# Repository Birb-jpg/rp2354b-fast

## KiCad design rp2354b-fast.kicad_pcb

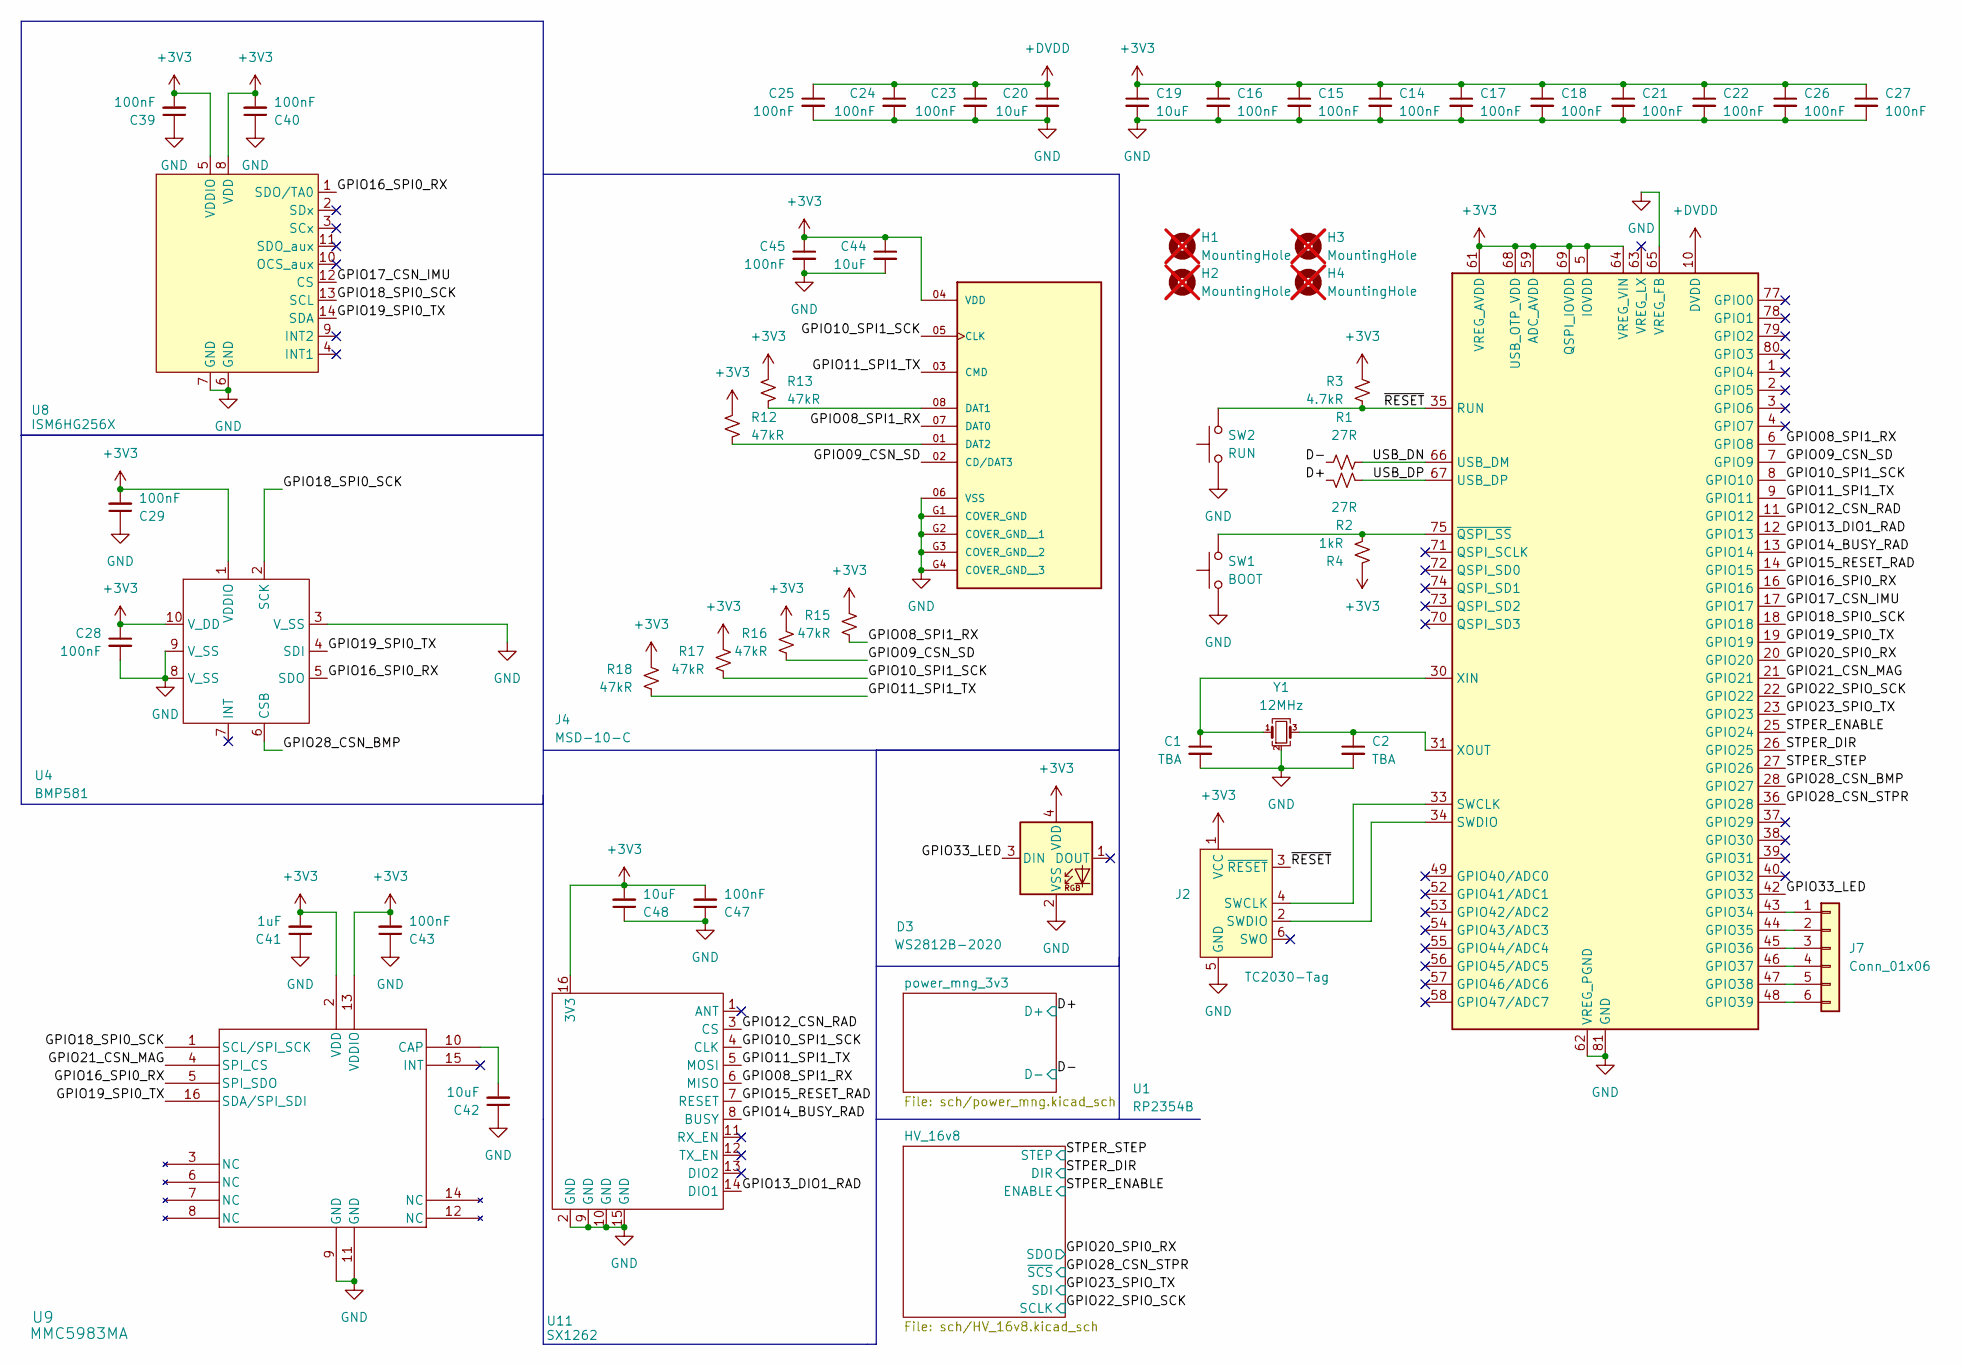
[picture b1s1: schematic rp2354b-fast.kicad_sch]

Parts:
C1, C2: TBA; C_0402_1005Metric
C14, C15, C16, C17, C18, C21, C22, C23, C24, C25, C26, C27, C28, C29, C39, C40, C43, C45, C47: 100nF; C_0402_1005Metric
C19, C20, C42, C44, C48: 10uF; C_0402_1005Metric
C41: 1uF; C_0402_1005Metric
D3: WS2812B-2020; LED_WS2812B-2020_PLCC4_2.0x2.0mm
H1, H2, H3, H4: MountingHole; MountingHole_4.3mm_M4; not fitted
J2: TC2030-Tag; Tag-Connect_TC2030-IDC-NL_2x03_P1.27mm_Vertical
J4: MSD-10-C; PARTREV 1.0
J7: Conn_01x06; PinHeader_1x06_P2.54mm_Vertical
R1, R2: 27R; R_0402_1005Metric
R3: 4.7kR; R_0402_1005Metric
R4: 1kR; R_0402_1005Metric
R12, R13, R15, R16, R17, R18: 47kR; R_0402_1005Metric
SW1: BOOT; SW_Push_1P1T_NO_Vertical_Wuerth_434133025816
SW2: RUN; SW_Push_1P1T_NO_Vertical_Wuerth_434133025816
U1: RP2354B; QFN-80-1EP_10x10mm_P0.4mm_EP3.4x3.4mm
U4: BMP581; QFN10_BMP581_BOS
U8: ISM6HG256X; LGA-14_3x2.5mm_P0.5mm_LayoutBorder3x4y
U9: MMC5983MA; LGA-16_3x3mm_P0.5mm
U11: SX1262; CORE-1262
Y1: 12MHz; Crystal_SMD_SeikoEpson_TSX3225-4Pin_3.2x2.5mm

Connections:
+3V3: C14.1, C15.1, C16.1, C17.1, C18.1, C19.1, C21.1, C22.1, C26.1, C27.1, C28.1, C29.2, C39.2, C40.2, C41.2, C43.2, C44.1, C45.1, C47.2, C48.2, D3.4 (VDD), J2.1 (VCC), J4.04 (VDD), R3.1, R4.1, R12.1, R13.1, R15.1, R16.1, R17.1, R18.1, U1.5 (IOVDD), U1.15 (IOVDD), U1.24 (IOVDD), U1.29 (IOVDD), U1.41 (IOVDD), U1.50 (IOVDD), U1.59 (ADC_AVDD), U1.60 (IOVDD), U1.61 (VREG_AVDD), U1.64 (VREG_VIN), U1.68 (USB_OTP_VDD), U1.69 (QSPI_IOVDD), U1.76 (IOVDD), U4.1 (VDDIO), U4.10 (V_DD), U8.5 (VDDIO), U8.8 (VDD), U9.2 (VDD), U9.13 (VDDIO), U11.16 (3V3); also elsewhere on the board
+DVDD: C20.1, C23.1, C24.1, C25.1, U1.10 (DVDD), U1.32 (DVDD), U1.51 (DVDD); also elsewhere on the board
/D+: R2.2; also elsewhere on the board
/D-: R1.2; also elsewhere on the board
/GPIO08_SPI1_RX: J4.07 (DAT0), R15.2, U1.6 (GPIO8), U11.6 (MISO)
/GPIO09_CSN_SD: J4.02 (CD/DAT3), R16.2, U1.7 (GPIO9)
/GPIO10_SPI1_SCK: J4.05 (CLK), R17.2, U1.8 (GPIO10), U11.4 (CLK)
/GPIO11_SPI1_TX: J4.03 (CMD), R18.2, U1.9 (GPIO11), U11.5 (MOSI)
/GPIO12_CSN_RAD: U1.11 (GPIO12), U11.3 (CS)
/GPIO13_DIO1_RAD: U1.12 (GPIO13), U11.14 (DIO1)
/GPIO14_BUSY_RAD: U1.13 (GPIO14), U11.8 (BUSY)
/GPIO15_RESET_RAD: U1.14 (GPIO15), U11.7 (RESET)
/GPIO16_SPI0_RX: U1.16 (GPIO16), U4.5 (SDO), U8.1 (SDO/TA0), U9.5 (SPI_SDO)
/GPIO17_CSN_IMU: U1.17 (GPIO17), U8.12 (CS)
/GPIO18_SPI0_SCK: U1.18 (GPIO18), U4.2 (SCK), U8.13 (SCL), U9.1 (SCL/SPI_SCK)
/GPIO19_SPI0_TX: U1.19 (GPIO19), U4.4 (SDI), U8.14 (SDA), U9.16 (SDA/SPI_SDI)
/GPIO20_SPI0_RX: U1.20 (GPIO20); also elsewhere on the board
/GPIO21_CSN_MAG: U1.21 (GPIO21), U9.4 (SPI_CS)
/GPIO22_SPIO_SCK: U1.22 (GPIO22); also elsewhere on the board
/GPIO23_SPIO_TX: U1.23 (GPIO23); also elsewhere on the board
/GPIO28_CSN_BMP: U1.28 (GPIO27), U4.6 (CSB)
/GPIO28_CSN_STPR: U1.36 (GPIO28); also elsewhere on the board
/GPIO33_LED: D3.3 (DIN), U1.42 (GPIO33)
/STPER_DIR: U1.26 (GPIO25); also elsewhere on the board
/STPER_ENABLE: U1.25 (GPIO24); also elsewhere on the board
/STPER_STEP: U1.27 (GPIO26); also elsewhere on the board
/USB_DN: R1.1, U1.66 (USB_DM)
/USB_DP: R2.1, U1.67 (USB_DP)
/~RESET: J2.3 (~RESET), R3.2, SW2.2, U1.35 (RUN)
GND: C1.2, C2.2, C14.2, C15.2, C16.2, C17.2, C18.2, C19.2, C20.2, C21.2, C22.2, C23.2, C24.2, C25.2, C26.2, C27.2, C28.2, C29.1, C39.1, C40.1, C41.1, C42.1, C43.1, C44.2, C45.2, C47.1, C48.1, D3.2 (VSS), J2.5 (GND), J4.06 (VSS), J4.G1 (COVER_GND), J4.G2 (COVER_GND__1), J4.G3 (COVER_GND__2), J4.G4 (COVER_GND__3), SW1.1, SW2.1, U1.62 (VREG_PGND), U1.65 (VREG_FB), U1.81 (GND), U4.3 (V_SS), U4.8 (V_SS), U4.9 (V_SS), U8.6 (GND), U8.7 (GND), U9.9 (GND), U9.11 (GND), U11.2 (GND), U11.9 (GND), U11.10 (GND), U11.15 (GND), Y1.2 (G), Y1.4 (G); also elsewhere on the board
unnamed: J2.4 (SWCLK), U1.33 (SWCLK)
unnamed: J2.2 (SWDIO), U1.34 (SWDIO)
unnamed: J4.08 (DAT1), R13.2
unnamed: J4.01 (DAT2), R12.2
unnamed: J7.1, U1.43 (GPIO34)
unnamed: J7.2, U1.44 (GPIO35)
unnamed: J7.3, U1.45 (GPIO36)
unnamed: J7.4, U1.46 (GPIO37)
unnamed: J7.5, U1.47 (GPIO38)
unnamed: J7.6, U1.48 (GPIO39)
unnamed: C1.1, U1.30 (XIN), Y1.1
unnamed: C2.1, U1.31 (XOUT), Y1.3
unnamed: R4.2, SW1.2, U1.75 (~QSPI_SS)
unnamed: C42.2, U9.10 (CAP)

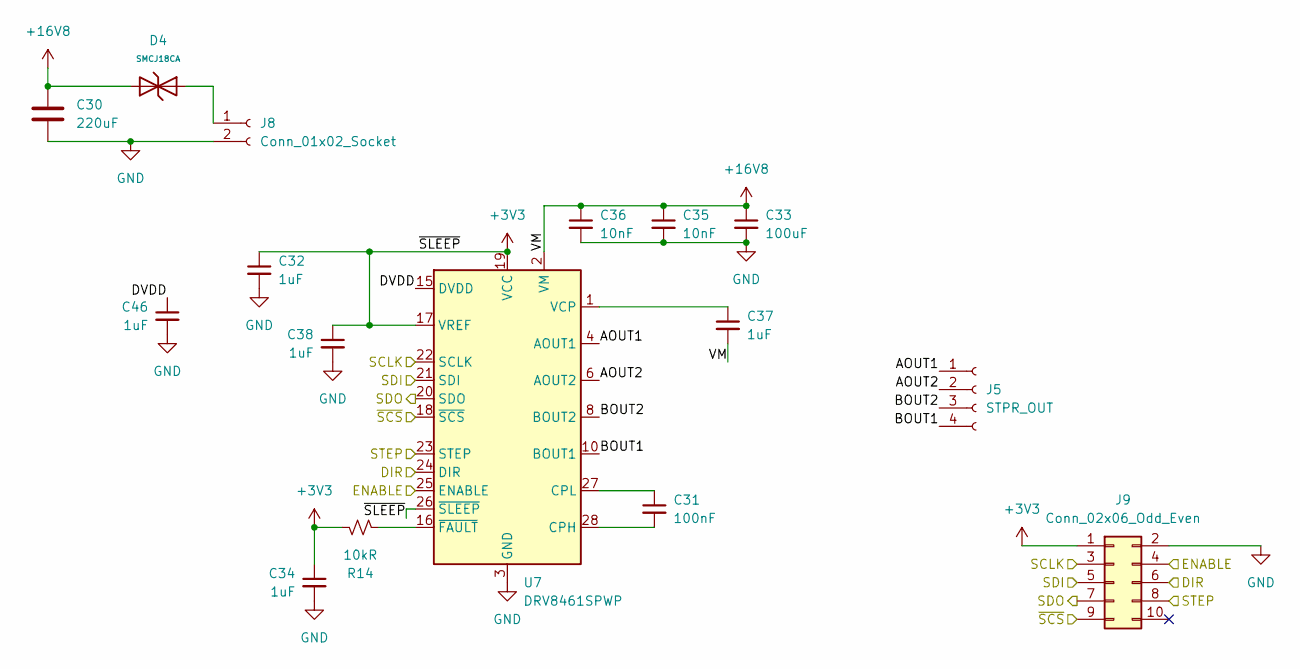
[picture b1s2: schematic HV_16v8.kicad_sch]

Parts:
C30: 220uF; CP_Radial_D8.0mm_P3.50mm
C31: 100nF; C_0402_1005Metric
C32, C34, C38, C46: 1uF; C_0402_1005Metric
C33: 100uF; C_1206_3216Metric
C35, C36: 10nF; C_1206_3216Metric
C37: 1uF; C_1206_3216Metric
D4: SMCJ18CA; D_SMC; Breakdown Voltage 22.1V; Part SMCJ18CA; LCSC C41411753
J5: STPR_OUT; JST_XA_B04B-XASK-1_1x04_P2.50mm_Vertical
J8: Conn_01x02_Socket; AMASS_XT30PW-M_1x02_P2.50mm_Horizontal
J9: Conn_02x06_Odd_Even; PinHeader_2x05_P2.54mm_Vertical
R14: 10kR; R_0402_1005Metric
U7: DRV8461SPWP; HTSSOP-28-1EP_4.4x9.7mm_P0.65mm_EP2.85x5.4mm_ThermalVias

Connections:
+3V3: C32.1, C34.1, C38.1, J9.1, R14.1, U7.17 (VREF), U7.19 (VCC), U7.26 (~SLEEP); also elsewhere on the board
+16V8: C30.1, C33.1, C35.1, C36.1, C37.2, D4.2, U7.2 (VM), U7.13 (VM)
/GPIO20_SPI0_RX: J9.7, U7.20 (SDO); also elsewhere on the board
/GPIO22_SPIO_SCK: J9.3, U7.22 (SCLK); also elsewhere on the board
/GPIO23_SPIO_TX: J9.5, U7.21 (SDI); also elsewhere on the board
/GPIO28_CSN_STPR: J9.9, U7.18 (~SCS); also elsewhere on the board
/HV_16v8/AOUT1: J5.1, U7.4 (AOUT1), U7.5 (AOUT1)
/HV_16v8/AOUT2: J5.2, U7.6 (AOUT2), U7.7 (AOUT2)
/HV_16v8/BOUT1: J5.4, U7.10 (BOUT1), U7.11 (BOUT1)
/HV_16v8/BOUT2: J5.3, U7.8 (BOUT2), U7.9 (BOUT2)
/HV_16v8/DVDD: C46.1, U7.15 (DVDD)
/STPER_DIR: J9.6, U7.24 (DIR); also elsewhere on the board
/STPER_ENABLE: J9.4, U7.25 (ENABLE); also elsewhere on the board
/STPER_STEP: J9.8, U7.23 (STEP); also elsewhere on the board
GND: C30.2, C32.2, C33.2, C34.2, C35.2, C36.2, C38.2, C46.2, J8.2, J9.2, U7.3 (GND), U7.12 (GND), U7.14 (GND), U7.29 (GND); also elsewhere on the board
unnamed: D4.1, J8.1
unnamed: C31.2, U7.28 (CPH)
unnamed: C31.1, U7.27 (CPL)
unnamed: C37.1, U7.1 (VCP)
unnamed: R14.2, U7.16 (~FAULT)

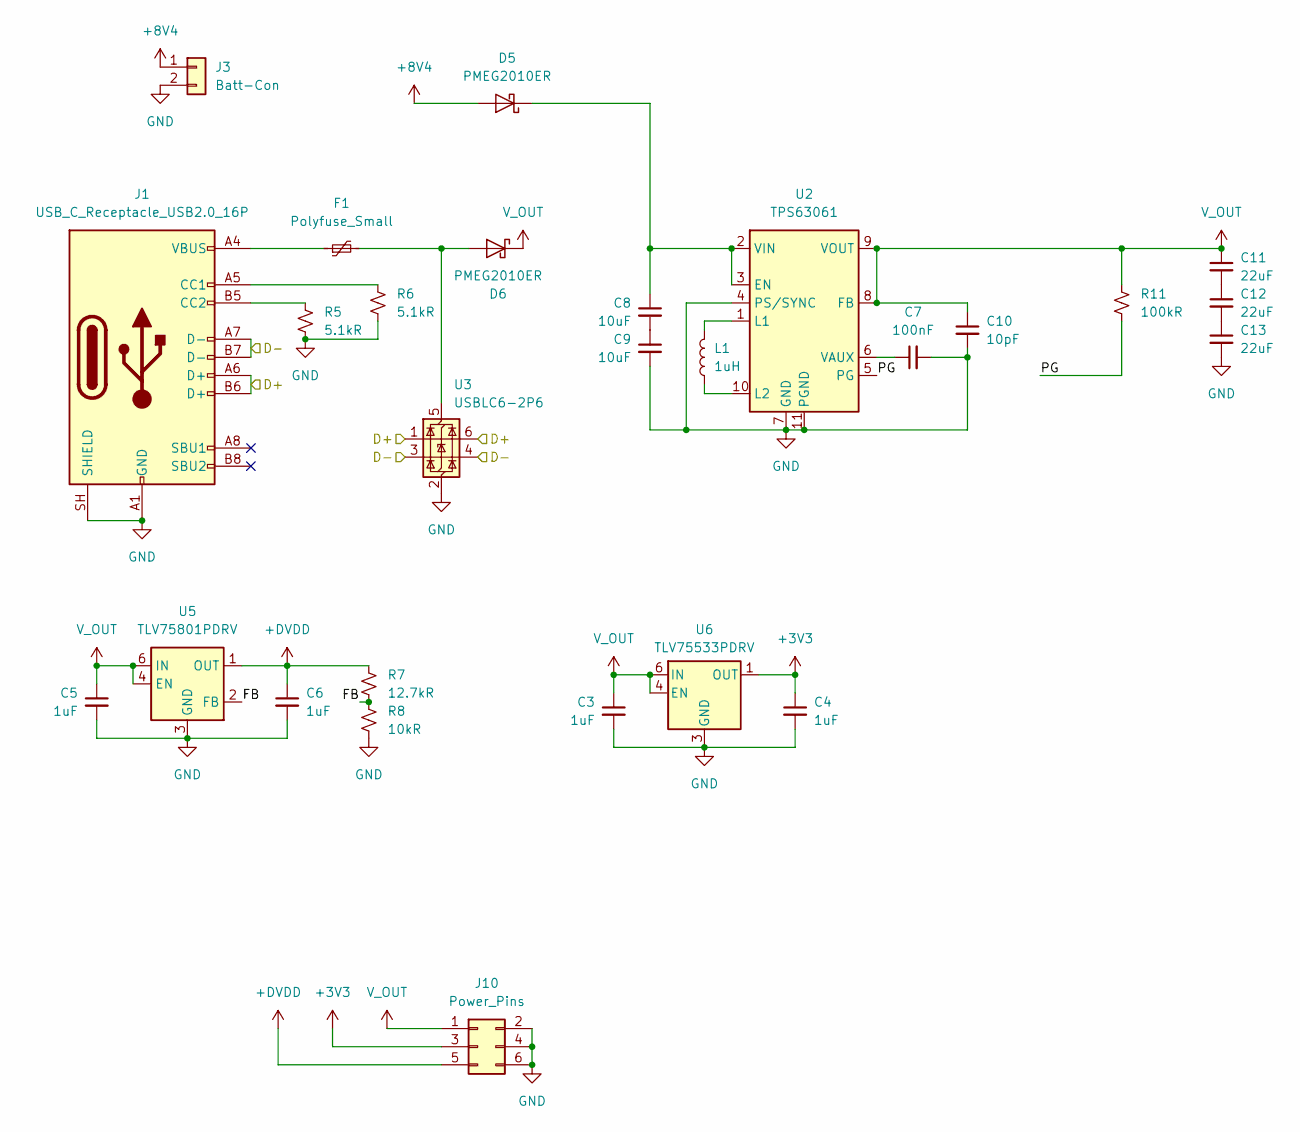
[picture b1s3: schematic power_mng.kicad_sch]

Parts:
C3, C4, C5, C6: 1uF; C_0402_1005Metric
C7: 100nF; C_0402_1005Metric
C8, C9: 10uF; C_0402_1005Metric
C10: 10pF; C_0402_1005Metric
C11, C12, C13: 22uF; C_0603_1608Metric
D5, D6: PMEG2010ER; Nexperia_CFP3_SOD-123W
F1: Polyfuse_Small; Fuse_0603_1608Metric
J1: USB_C_Receptacle_USB2.0_16P; USB_C_Receptacle_HRO_TYPE-C-31-M-12
J3: Batt-Con; AMASS_XT30PW-M_1x02_P2.50mm_Horizontal
J10: Power_Pins; PinHeader_2x03_P2.54mm_Vertical
L1: 1uH; L_Coilcraft_XxL4020
R5, R6: 5.1kR; R_0402_1005Metric
R7: 12.7kR; R_0402_1005Metric
R8: 10kR; R_0402_1005Metric
R11: 100kR; R_0402_1005Metric
U2: TPS63061; Texas_S-PWSON-N10_ThermalVias
U3: USBLC6-2P6; SOT-666
U5: TLV75801PDRV; WSON-6-1EP_2x2mm_P0.65mm_EP1x1.6mm
U6: TLV75533PDRV; WSON-6-1EP_2x2mm_P0.65mm_EP1x1.6mm

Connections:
+3V3: C4.1, J10.3, U6.1 (OUT); also elsewhere on the board
+8V4: D5.2 (A), J3.1
+DVDD: C6.1, J10.5, R7.2, U5.1 (OUT); also elsewhere on the board
/D+: J1.A6 (D+), J1.B6 (D+), U3.1 (I/O1), U3.6 (I/O1); also elsewhere on the board
/D-: J1.A7 (D-), J1.B7 (D-), U3.3 (I/O2), U3.4 (I/O2); also elsewhere on the board
/power_mng_3v3/FB: R7.1, R8.2, U5.2 (FB)
/power_mng_3v3/PG: R11.1, U2.5 (PG)
GND: C3.2, C4.2, C5.2, C6.2, C7.2, C9.2, C10.2, C13.2, J1.A1 (GND), J1.A12 (GND), J1.B1 (GND), J1.B12 (GND), J1.SH (SHIELD), J3.2, J10.2, J10.4, J10.6, R5.1, R6.1, R8.1, U2.4 (PS/SYNC), U2.7 (GND), U2.11 (PGND), U3.2 (GND), U5.3 (GND), U5.7 (GND), U6.3 (GND), U6.7 (GND); also elsewhere on the board
unnamed: C8.2, C9.1
unnamed: C11.2, C12.1
unnamed: C12.2, C13.1
unnamed: C8.1, D5.1 (K), U2.2 (VIN), U2.3 (EN)
unnamed: D6.2 (A), F1.2, U3.5 (VBUS)
unnamed: F1.1, J1.A4 (VBUS), J1.A9 (VBUS), J1.B4 (VBUS), J1.B9 (VBUS)
unnamed: J1.A5 (CC1), R6.2
unnamed: J1.B5 (CC2), R5.2
unnamed: L1.2, U2.1 (L1)
unnamed: L1.1, U2.10 (L2)
unnamed: C7.1, U2.6 (VAUX)
V_OUT: C3.1, C5.1, C10.1, C11.1, D6.1 (K), J10.1, R11.2, U2.8 (FB), U2.9 (VOUT), U5.4 (EN), U5.6 (IN), U6.4 (EN), U6.6 (IN)

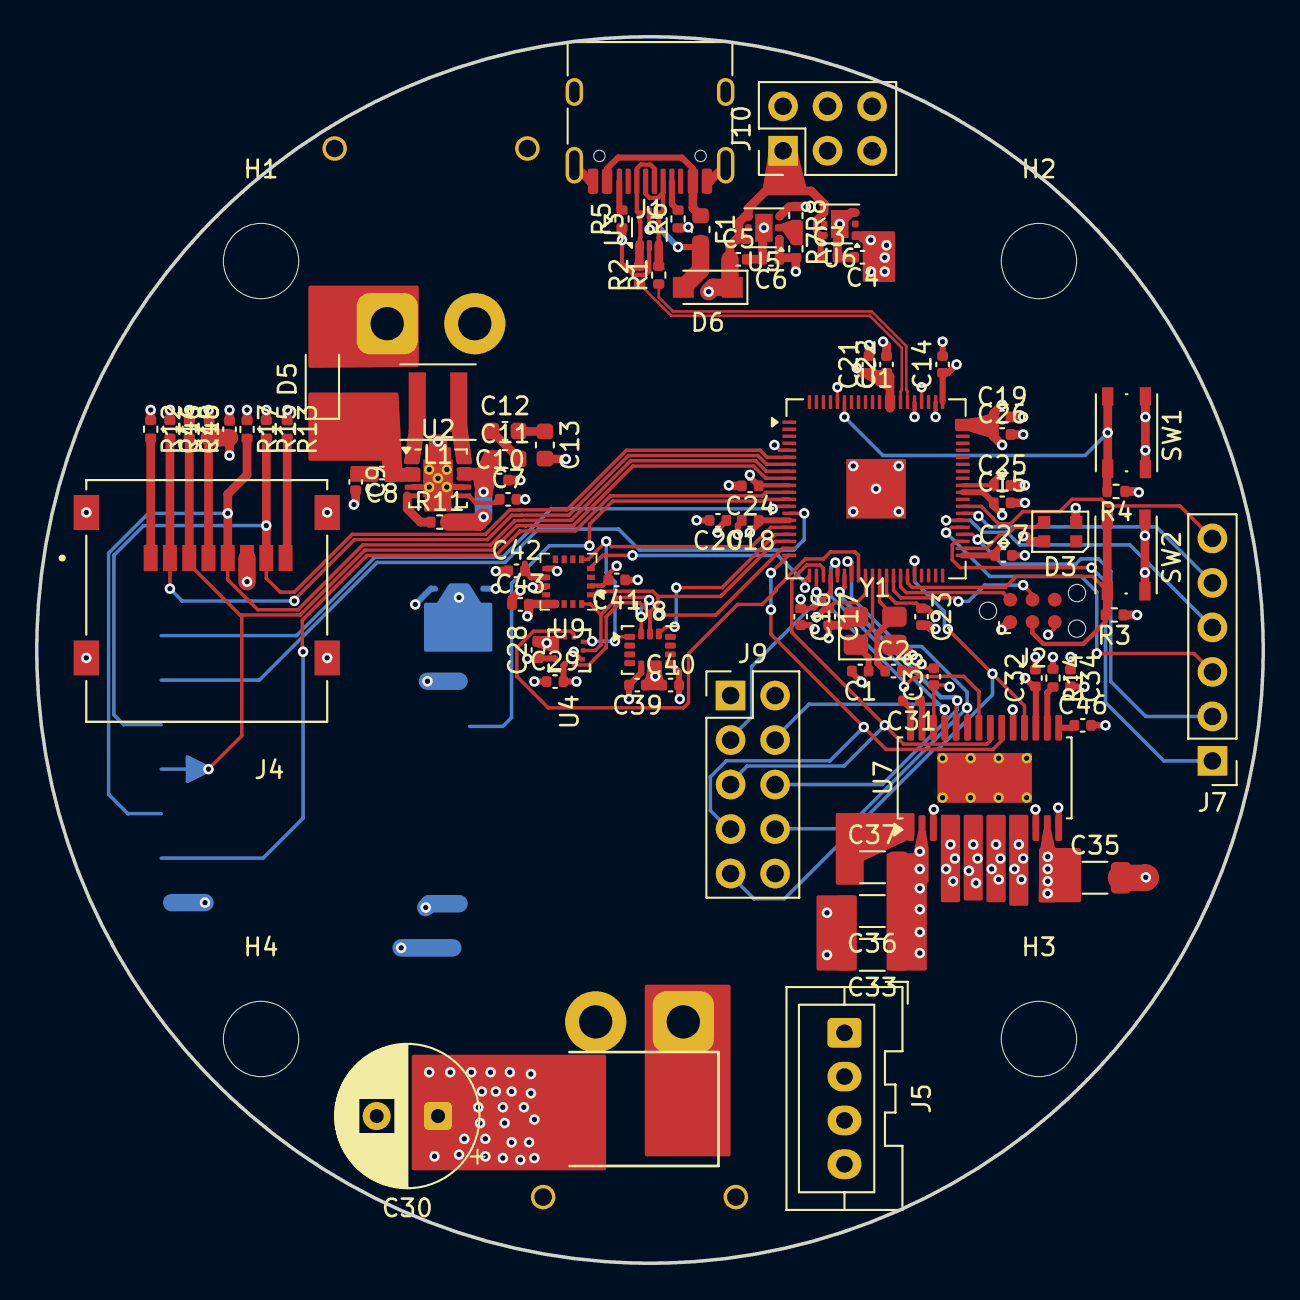
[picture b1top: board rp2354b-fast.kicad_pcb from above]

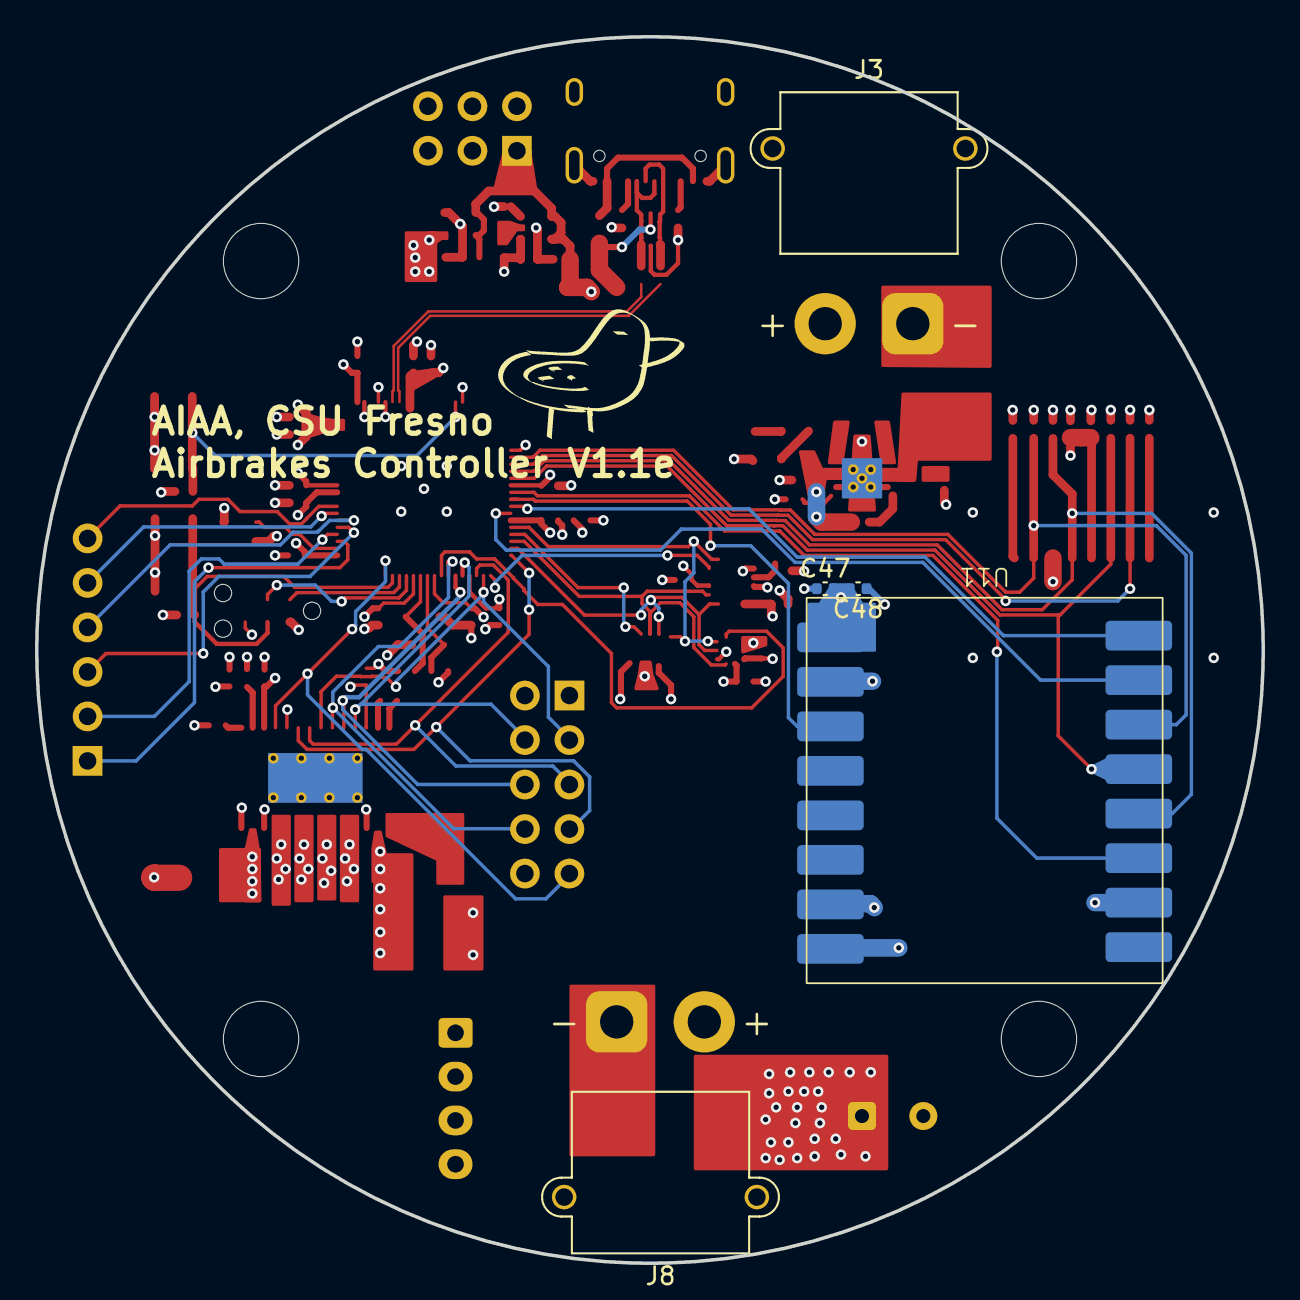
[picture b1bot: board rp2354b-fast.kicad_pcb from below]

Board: 4 copper layers, 70.0 x 70.0 mm, 96 parts (5 on the bottom side), 70 nets.

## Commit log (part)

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2026-06-29 init schematic
    yurp
2026-06-29 routes
2026-06-30 footprint
2026-06-30 routes and bmp581
2026-06-30 hv16v
2026-06-30 imu sym
